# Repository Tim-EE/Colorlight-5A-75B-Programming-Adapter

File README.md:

# Colorlight-5A-75B-Programming-Adapter

A programming adapter to use either a USB Blaster or FT230X to program the FPGA on the Colorlight 5A-75B.

This design is intended to use the USB Blaster to program the ECP5 FPGA on the Colorlight 5A-75B and with the option of using a FT230X, provided the functionality is built out.

Note: The FT230X approach hasn't been developed. I included it here for future development.

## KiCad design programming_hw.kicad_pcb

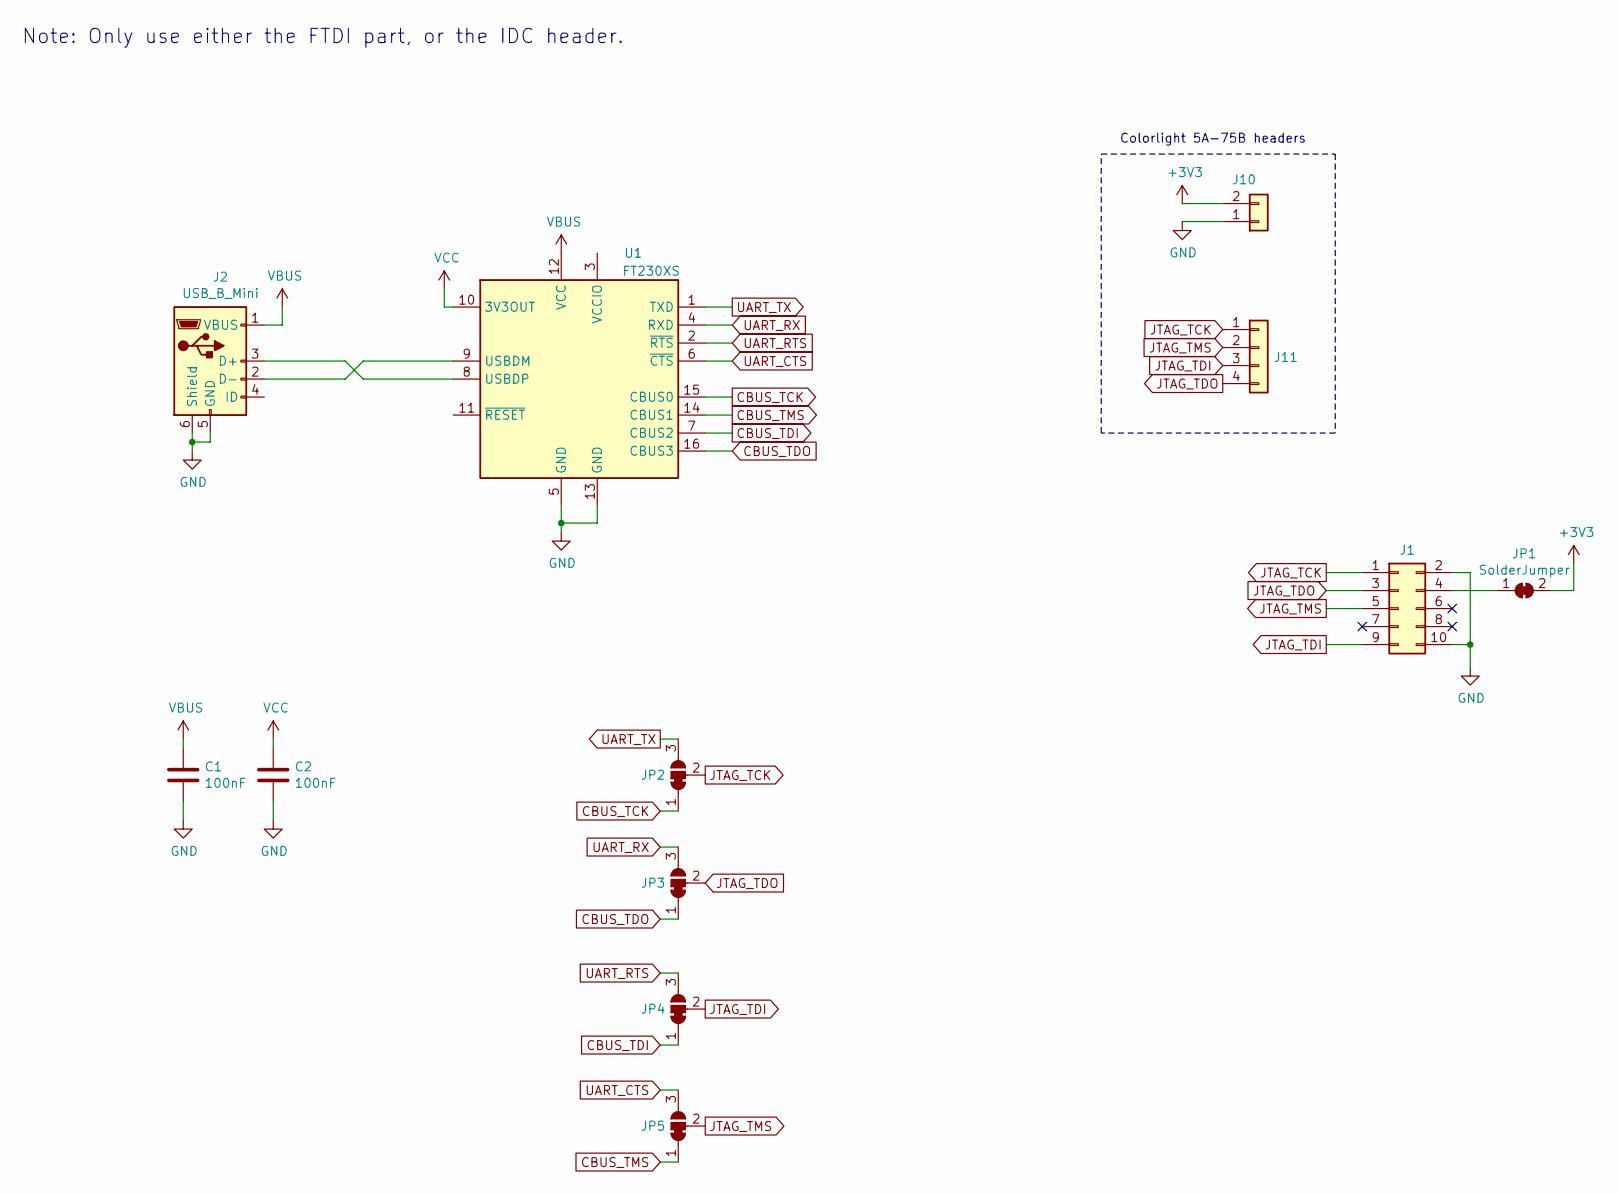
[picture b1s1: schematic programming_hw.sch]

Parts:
C1, C2: 100nF; C_0805_2012Metric_Pad1.15x1.40mm_HandSolder
J1: Conn_02x05_Odd_Even; IDC-Header_2x05_P2.54mm_Vertical
J2: USB_B_Mini; USB_Mini-B_Wuerth_65100516121_Horizontal
J10: Conn_01x02; PinSocket_1x02_P2.54mm_Vertical
J11: Conn_01x04; PinSocket_1x04_P2.54mm_Vertical
JP1: SolderJumper; SolderJumper-2_P1.3mm_Bridged_RoundedPad1.0x1.5mm
JP2, JP3, JP4, JP5: SolderJumper_3_Bridged12; SolderJumper-3_P1.3mm_Bridged12_RoundedPad1.0x1.5mm_NumberL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
U1: FT230XS; SSOP-16_3.9x4.9mm_P0.635mm

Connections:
+3V3: J10.2, JP1.2 (B)
CBUS_TCK: JP2.1 (A), U1.15 (CBUS0)
CBUS_TDI: JP4.1 (A), U1.7 (CBUS2)
CBUS_TDO: JP3.1 (A), U1.16 (CBUS3)
CBUS_TMS: JP5.1 (A), U1.14 (CBUS1)
GND: C1.2, C2.2, J1.2, J1.10, J2.5 (GND), J2.6 (Shield), J10.1, U1.5 (GND), U1.13 (GND)
JTAG_TCK: J1.1, J11.1, JP2.2 (C)
JTAG_TDI: J1.9, J11.3, JP4.2 (C)
JTAG_TDO: J1.3, J11.4, JP3.2 (C)
JTAG_TMS: J1.5, J11.2, JP5.2 (C)
unnamed: J1.4, JP1.1 (A)
unnamed: J2.2 (D-), U1.9 (USBDM)
unnamed: J2.3 (D+), U1.8 (USBDP)
UART_CTS: JP5.3 (B), U1.6 (~CTS)
UART_RTS: JP4.3 (B), U1.2 (~RTS)
UART_RX: JP3.3 (B), U1.4 (RXD)
UART_TX: JP2.3 (B), U1.1 (TXD)
VBUS: C1.1, J2.1 (VBUS), U1.12 (VCC)
VCC: C2.1, U1.10 (3V3OUT)

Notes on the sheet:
Colorlight 5A-75B headers
Note: Only use either the FTDI part, or the IDC header.

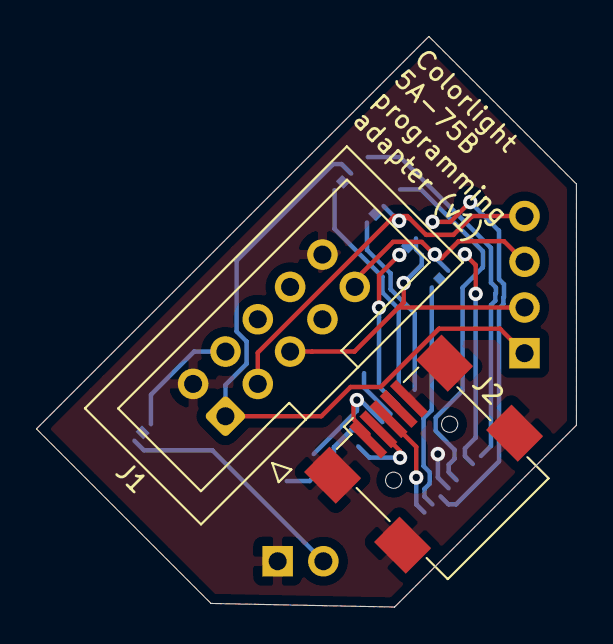
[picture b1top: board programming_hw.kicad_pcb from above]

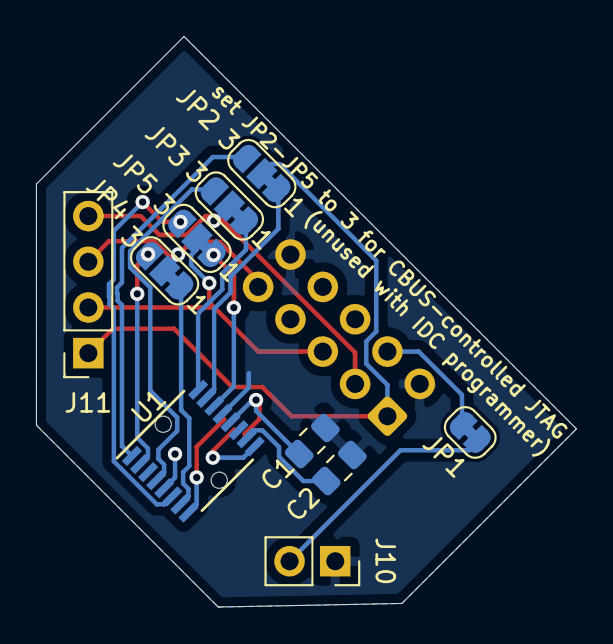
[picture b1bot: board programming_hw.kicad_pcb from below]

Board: 2 copper layers, 30.0 x 31.7 mm, 12 parts (10 on the bottom side), 19 nets.
